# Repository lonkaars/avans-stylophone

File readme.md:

# avans-stylofoon

(dutch)

bronnen voor project stylofoon van technische informatica bij hogeschool avans
in den bosch. hier staan alle kicad bestanden voor de elektrische schema's en
hardwareontwerpen, en alle documentatie die ingeleverd moet worden.

## advies voor andere studenten die dit project ook moeten doen

- Lees goed wat de 'gain' van de LM386 doet
- Maak je system requirements een beetje vaag (zie mijn system requirements),
	zo verlies je geen punten wanneer het uiteidendelijk blijkt dat je stylofoon
	ontzettend vals klinkt omdat de weerstanden niet helemaal kloppen
- Uitbereidingen zijn leuk, maar als ik het project opnieuw zou doen zou ik
	gewoon voor de 8 drukknoppen en shiftregister gaan, want uitbereidingen maken
	bij de stylofoon is lastig
- Onderzoek goed hoe je een constante 'drone'-toon kan vermijden (als je gaat
	voor de vco opstelling van de 555, de rco is hier waarschijnlijk niet
	gevoelig voor), anders maakt je stylofoon een contstante middentoon, inplaats
	van dat het stil is als je geen toets aanspeelt
- Er staan Sony speakers in het techlab, deze werken (in mijn geval slecht) en
	zorgde er (onder andere) voor dat mijn VU-display het niet goed deed.
- Speaker specificaties verschillen niet alleen in impedantie, maar ook enorm
	in gevoeligheid, dus het kan makkelijk aan de speaker liggen als je stylofoon
	geen 'fatsoenlijk volume' produceert.
- Maak veel system tests voor dingen die toch wel zullen werken, uiteidenlijk
	word je eindcijfer voor werking bepaald door het percentage van behaalde
	system tests, en onder de 90% geeft je al een 4. Dus als je bijvoorbeeld 18
	tests hebt kun je er maar 1 missen om nog een voldoende te halen.

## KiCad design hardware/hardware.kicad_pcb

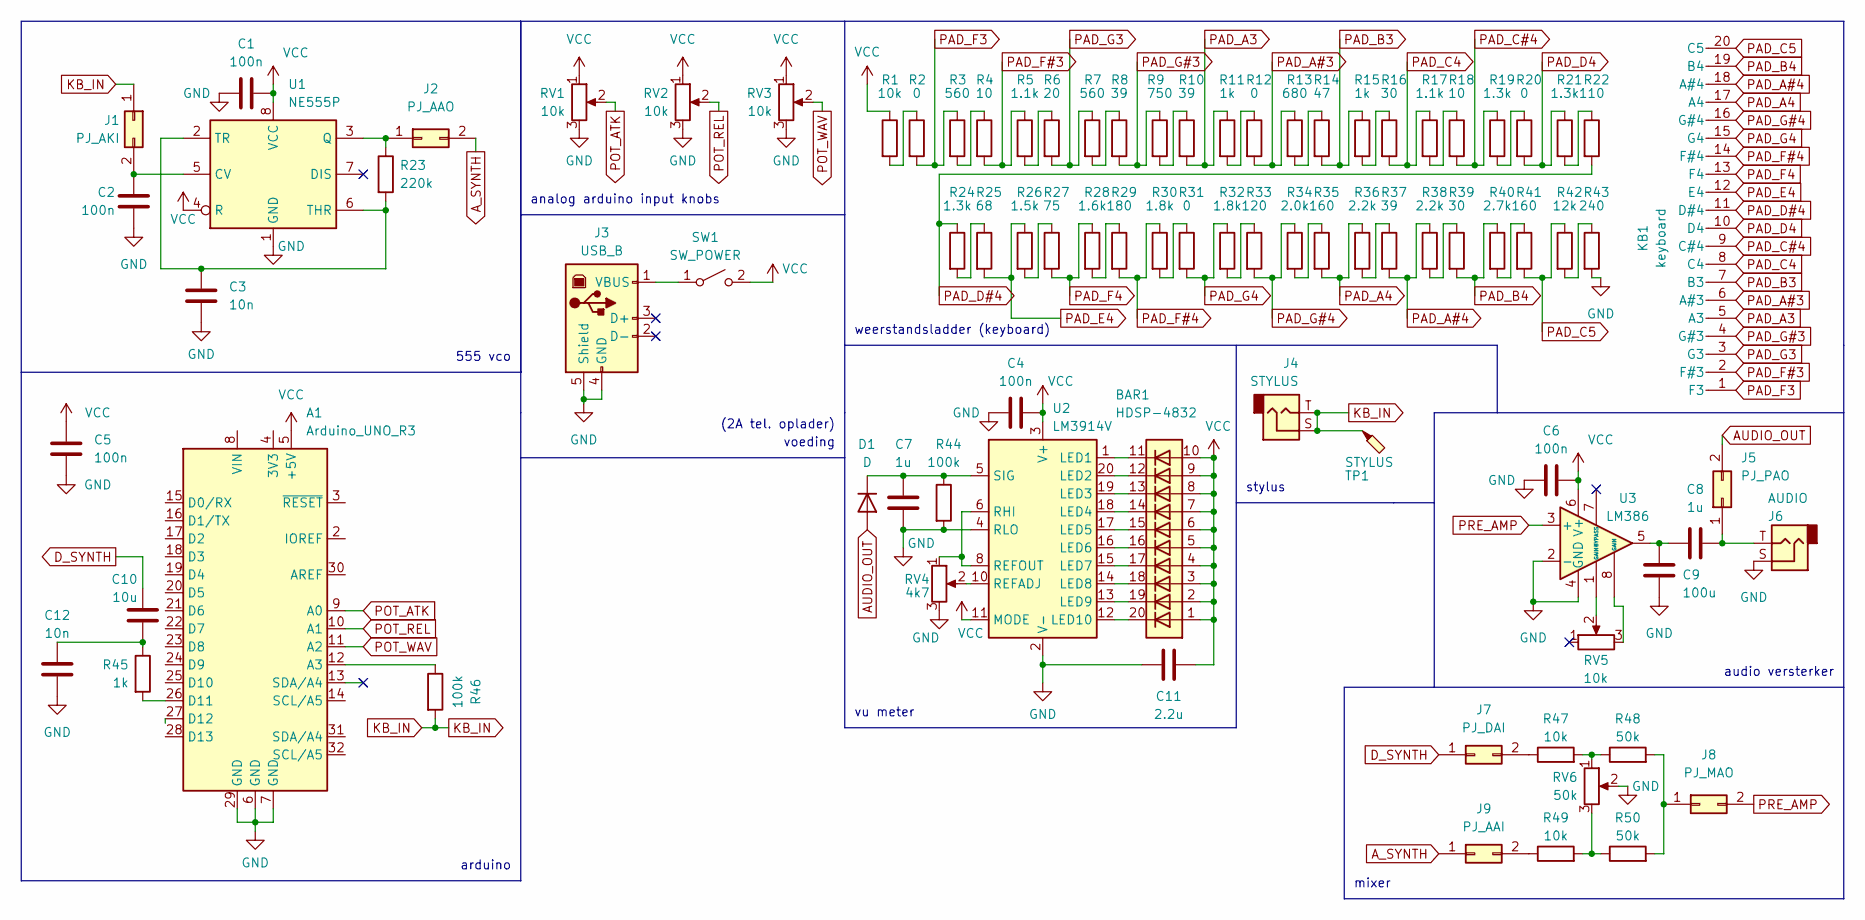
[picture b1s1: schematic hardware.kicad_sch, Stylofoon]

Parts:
A1: Arduino_UNO_R3
BAR1: HDSP-4832
C1, C2, C4, C5, C6: 100n; C_Disc_D3.0mm_W1.6mm_P2.50mm
C3, C12: 10n; C_Disc_D3.0mm_W1.6mm_P2.50mm
C7, C8: 1u; CP_Radial_D5.0mm_P2.00mm
C9: 100u; CP_Radial_D10.0mm_P2.50mm
C10: 10u; CP_Radial_D10.0mm_P2.50mm
C11: 2.2u; CP_Radial_D5.0mm_P2.00mm
D1: D; D_A-405_P7.62mm_Horizontal
J1: PJ_AKI; PinHeader_1x02_P2.54mm_Vertical
J2: PJ_AAO; PinHeader_1x02_P2.54mm_Vertical
J3: USB_B; USB_B_Lumberg_2411_02_Horizontal
J4: STYLUS; Jack_3.5mm_Ledino_KB3SPRS_Horizontal
J5: PJ_PAO; PinHeader_1x02_P2.54mm_Vertical
J6: AUDIO; Jack_3.5mm_Ledino_KB3SPRS_Horizontal
J7: PJ_DAI; PinHeader_1x02_P2.54mm_Vertical
J8: PJ_MAO; PinHeader_1x02_P2.54mm_Vertical
J9: PJ_AAI; PinHeader_1x02_P2.54mm_Vertical
KB1: keyboard
R1, R47, R49: 10k; R_Axial_DIN0207_L6.3mm_D2.5mm_P10.16mm_Horizontal
R2, R12, R20, R31: 0; R_Axial_DIN0207_L6.3mm_D2.5mm_P10.16mm_Horizontal
R3, R7: 560; R_Axial_DIN0207_L6.3mm_D2.5mm_P10.16mm_Horizontal
R4, R18: 10; R_Axial_DIN0207_L6.3mm_D2.5mm_P10.16mm_Horizontal
R5, R17: 1.1k; R_Axial_DIN0207_L6.3mm_D2.5mm_P10.16mm_Horizontal
R6: 20; R_Axial_DIN0207_L6.3mm_D2.5mm_P10.16mm_Horizontal
R8, R10, R37: 39; R_Axial_DIN0207_L6.3mm_D2.5mm_P10.16mm_Horizontal
R9: 750; R_Axial_DIN0207_L6.3mm_D2.5mm_P10.16mm_Horizontal
R11, R15, R45: 1k; R_Axial_DIN0207_L6.3mm_D2.5mm_P10.16mm_Horizontal
R13: 680; R_Axial_DIN0207_L6.3mm_D2.5mm_P10.16mm_Horizontal
R14: 47; R_Axial_DIN0207_L6.3mm_D2.5mm_P10.16mm_Horizontal
R16, R39: 30; R_Axial_DIN0207_L6.3mm_D2.5mm_P10.16mm_Horizontal
R19, R21, R24: 1.3k; R_Axial_DIN0207_L6.3mm_D2.5mm_P10.16mm_Horizontal
R22: 110; R_Axial_DIN0207_L6.3mm_D2.5mm_P10.16mm_Horizontal
R23: 220k; R_Axial_DIN0207_L6.3mm_D2.5mm_P10.16mm_Horizontal
R25: 68; R_Axial_DIN0207_L6.3mm_D2.5mm_P10.16mm_Horizontal
R26: 1.5k; R_Axial_DIN0207_L6.3mm_D2.5mm_P10.16mm_Horizontal
R27: 75; R_Axial_DIN0207_L6.3mm_D2.5mm_P10.16mm_Horizontal
R28: 1.6k; R_Axial_DIN0207_L6.3mm_D2.5mm_P10.16mm_Horizontal
R29: 180; R_Axial_DIN0207_L6.3mm_D2.5mm_P10.16mm_Horizontal
R30, R32: 1.8k; R_Axial_DIN0207_L6.3mm_D2.5mm_P10.16mm_Horizontal
R33: 120; R_Axial_DIN0207_L6.3mm_D2.5mm_P10.16mm_Horizontal
R34: 2.0k; R_Axial_DIN0207_L6.3mm_D2.5mm_P10.16mm_Horizontal
R35, R41: 160; R_Axial_DIN0207_L6.3mm_D2.5mm_P10.16mm_Horizontal
R36, R38: 2.2k; R_Axial_DIN0207_L6.3mm_D2.5mm_P10.16mm_Horizontal
R40: 2.7k; R_Axial_DIN0207_L6.3mm_D2.5mm_P10.16mm_Horizontal
R42: 12k; R_Axial_DIN0207_L6.3mm_D2.5mm_P10.16mm_Horizontal
R43: 240; R_Axial_DIN0207_L6.3mm_D2.5mm_P10.16mm_Horizontal
R44, R46: 100k; R_Axial_DIN0207_L6.3mm_D2.5mm_P10.16mm_Horizontal
R48, R50: 50k; R_Axial_DIN0207_L6.3mm_D2.5mm_P10.16mm_Horizontal
RV1, RV2, RV3, RV5: 10k; potm
RV4: 4k7; Potentiometer_Piher_PT-10-V10_Vertical
RV6: 50k; potm
SW1: SW_POWER; SW_Slide_1P2T_CK_OS102011MS2Q
TP1: STYLUS
U1: NE555P; DIP-8_W7.62mm
U2: LM3914V; avans-lm3914v
U3: LM386; DIP-8_W7.62mm

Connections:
AUDIO_OUT: D1.2 (A), J5.2
A_SYNTH: J2.2, J9.1
D_SYNTH: C10.1, J7.1
GND: A1.6 (GND), A1.7 (GND), A1.29 (GND), C1.1, C2.2, C3.2, C4.1, C5.1, C6.1, C7.2, C9.2, C11.2, C12.2, J3.4 (GND), J3.5 (Shield), J6.S, R43.2, R44.2, RV1.3, RV2.3, RV3.3, RV4.3, RV6.2, U1.1 (GND), U2.2 (V-), U2.4 (RLO), U3.2 (-), U3.4 (GND)
KB_IN: J1.1, J4.S, J4.T, R46.2, TP1.1
unnamed: A1.12 (A3), R46.1
unnamed: A1.26 (D11), R45.2
unnamed: BAR1.11 (K), U2.1 (LED1)
unnamed: BAR1.12 (K), U2.20 (LED2)
unnamed: BAR1.13 (K), U2.19 (LED3)
unnamed: BAR1.14 (K), U2.18 (LED4)
unnamed: BAR1.15 (K), U2.17 (LED5)
unnamed: BAR1.16 (K), U2.16 (LED6)
unnamed: BAR1.17 (K), U2.15 (LED7)
unnamed: BAR1.18 (K), U2.14 (LED8)
unnamed: BAR1.19 (K), U2.13 (LED9)
unnamed: BAR1.20 (K), U2.12 (LED10)
unnamed: C2.1, J1.2, U1.5 (CV)
unnamed: C3.1, R23.2, U1.2 (TR), U1.6 (THR)
unnamed: C7.1, D1.1 (K), R44.1, U2.5 (SIG)
unnamed: C8.1, C9.1, U3.5
unnamed: C8.2, J5.1, J6.T
unnamed: C10.2, C12.1, R45.1
unnamed: J2.1, R23.1, U1.3 (Q)
unnamed: J3.1 (VBUS), SW1.1 (A)
unnamed: J7.2, R47.1
unnamed: J8.1, R48.2, R50.2
unnamed: J9.2, R49.1
unnamed: R1.2, R2.1
unnamed: R3.2, R4.1
unnamed: R5.2, R6.1
unnamed: R7.2, R8.1
unnamed: R9.2, R10.1
unnamed: R11.2, R12.1
unnamed: R13.2, R14.1
unnamed: R15.2, R16.1
unnamed: R17.2, R18.1
unnamed: R19.2, R20.1
unnamed: R21.2, R22.1
unnamed: R24.2, R25.1
unnamed: R26.2, R27.1
unnamed: R28.2, R29.1
unnamed: R30.2, R31.1
unnamed: R32.2, R33.1
unnamed: R34.2, R35.1
unnamed: R36.2, R37.1
unnamed: R38.2, R39.1
unnamed: R40.2, R41.1
unnamed: R42.2, R43.1
unnamed: R47.2, R48.1, RV6.1
unnamed: R49.2, R50.1, RV6.3
unnamed: RV4.1, U2.6 (RHI), U2.8 (REFOUT)
unnamed: RV4.2, U2.10 (REFADJ)
unnamed: RV5.2, U3.1 (GAIN)
unnamed: RV5.3, U3.8 (GAIN)
PAD_A3: KB1.5 (A3), R10.2, R11.1
PAD_A4: KB1.17 (A4), R35.2, R36.1
PAD_A#3: KB1.6 (A#3), R12.2, R13.1
PAD_A#4: KB1.18 (A#4), R37.2, R38.1
PAD_B3: KB1.7 (B3), R14.2, R15.1
PAD_B4: KB1.19 (B4), R39.2, R40.1
PAD_C4: KB1.8 (C4), R16.2, R17.1
PAD_C5: KB1.20 (C5), R41.2, R42.1
PAD_C#4: KB1.9 (C#4), R18.2, R19.1
PAD_D4: KB1.10 (D4), R20.2, R21.1
PAD_D#4: KB1.11 (D#4), R22.2, R24.1
PAD_E4: KB1.12 (E4), R25.2, R26.1
PAD_F3: KB1.1 (F3), R2.2, R3.1
PAD_F4: KB1.13 (F4), R27.2, R28.1
PAD_F#3: KB1.2 (F#3), R4.2, R5.1
PAD_F#4: KB1.14 (F#4), R29.2, R30.1
PAD_G3: KB1.3 (G3), R6.2, R7.1
PAD_G4: KB1.15 (G4), R31.2, R32.1
PAD_G#3: KB1.4 (G#3), R8.2, R9.1
PAD_G#4: KB1.16 (G#4), R33.2, R34.1
POT_ATK: A1.9 (A0), RV1.2
POT_REL: A1.10 (A1), RV2.2
POT_WAV: A1.11 (A2), RV3.2
PRE_AMP: J8.2, U3.3 (+)
VCC: A1.5 (+5V), BAR1.1 (A), BAR1.2 (A), BAR1.3 (A), BAR1.4 (A), BAR1.5 (A), BAR1.6 (A), BAR1.7 (A), BAR1.8 (A), BAR1.9 (A), BAR1.10 (A), C1.2, C4.2, C5.2, C6.2, C11.1, R1.1, RV1.1, RV2.1, RV3.1, SW1.2 (B), U1.4 (R), U1.8 (VCC), U2.3 (V+), U2.11 (MODE), U3.6 (V+)

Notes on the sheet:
arduino
555 vco
analog arduino input knobs
vu meter
audio versterker
voeding
mixer
(2A tel. oplader)
stylus
weerstandsladder (keyboard)

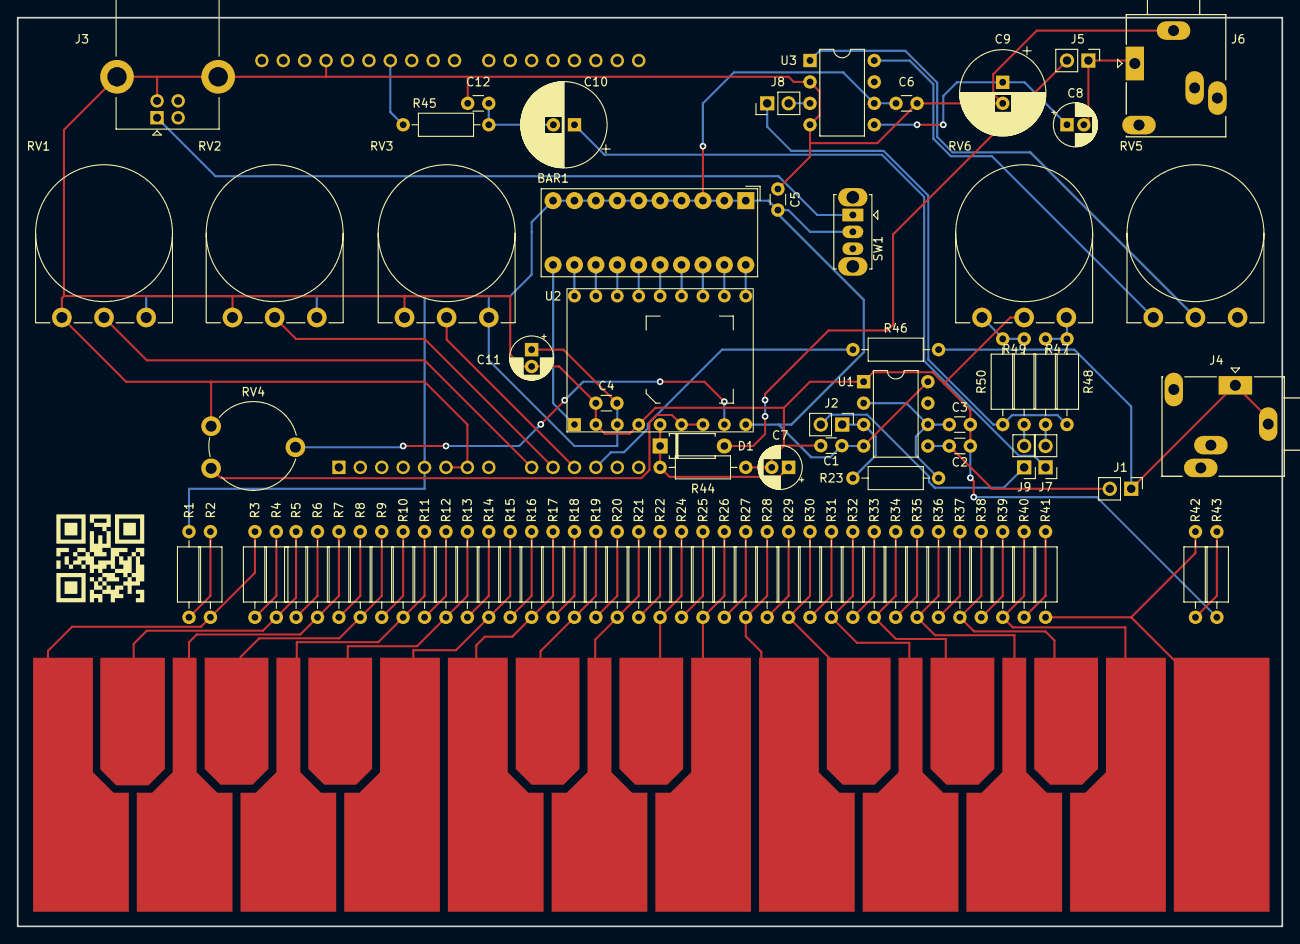
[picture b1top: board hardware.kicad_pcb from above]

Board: 2 copper layers, 150.0 x 107.8 mm, 85 parts (1 on the bottom side), 80 nets.

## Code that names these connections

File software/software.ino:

#include "lib/the_synth/synth.h"

#define KB_SAMPLES 100
#define PINOUT_AUDIO_OUT CHA
#define PINOUT_POT_ATK A0
#define PINOUT_POT_REL A1
#define PINOUT_POT_WAV A2
#define PINOUT_KB_IN A3

synth bernard;

void setup() {
	// i/o instellen
	pinMode(PINOUT_AUDIO_OUT, OUTPUT);
	pinMode(PINOUT_POT_ATK, INPUT);
	pinMode(PINOUT_POT_WAV, INPUT);
	pinMode(PINOUT_POT_REL, INPUT);
	pinMode(PINOUT_KB_IN, INPUT);

	// the_synth initialiseren
	bernard.begin(PINOUT_AUDIO_OUT);

	// gekopiëerd van een stukje voorbeeldcode, alleen de golfvorm maakt hier uit
	bernard.setupVoice(0,SINE,60,ENVELOPE0,90,64);
	bernard.setupVoice(1,TRIANGLE,62,ENVELOPE1,90,64);
	bernard.setupVoice(2,SAW,64,ENVELOPE2,90,64);
	bernard.setupVoice(3,SQUARE,67,ENVELOPE0,90,64);
}

void loop() {
	// lees potmeters uit
	unsigned int pot_rel = analogRead(PINOUT_POT_REL);
	unsigned int pot_atk = analogRead(PINOUT_POT_ATK);
	unsigned int pot_wav = analogRead(PINOUT_POT_WAV);

	// neem een gemiddelde meting van de keyboard ingangsspanning
	double average = 0.0;
	for (int i = 0; i < KB_SAMPLES; i++)
		average += ((double) analogRead(PINOUT_KB_IN)) / KB_SAMPLES;

	// geplukte getallen om de klank aan te passen
	unsigned char env = pot_rel / (1024/4);
	unsigned char mod = 572 + pot_atk / 100;
	unsigned char wave = pot_wav / (1024/4);

	// synth kiezen / klank bijwerken
	bernard.setEnvelope(wave, env);
	// synth triggeren
	bernard.mTrigger(wave, 116 - average / 10);
	delay(500 - pot_atk / 5);
}

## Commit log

2022-02-07 made some system requirements
2022-02-07 added incomplete wbs diagram
2022-02-12 finish system requirements
2022-02-12 work breakdown structure done
2022-02-12 system test document done
2022-02-12 added name to wbs and added block diagram
2022-02-15 added (incomplete) tests
2022-02-15 research document starting point
2022-02-17 more research
2022-02-19 more test schematics
2022-02-19 diagrams
2022-02-21 updated block diagrams
2022-02-21 partitioning schematics
2022-02-21 mode hardware tests
2022-02-21 test arduino sketch
2022-02-21 meer kritiek :)
2022-02-22 added lab tests
2022-02-22 measurements
2022-02-22 electric schematics and typo fix
2022-02-22 fix markdown table
2022-02-23 more measurements
2022-02-27 more work
2022-03-08 more schematics
2022-03-09 more hardware
2022-03-10 more hardware
    amplifier circuit done
2022-03-10 more hardware (almost done!)
2022-03-12 hardware done
2022-03-12 final hardware version
2022-03-24 hardware gesoldeerd
2022-04-01 more hardwre debugging
2022-04-02 clean up software and begin design document
2022-04-03 ontwerpdocument
2022-04-04 beginsel presentatie
2022-04-05 presentatie
2022-04-06 document revision
2022-04-06 urenrapportage en advies voor medestudenten toegevoegd
2022-04-06 dia's in verkeerde volgorde
2022-04-07 added image of finished and assembled pcb
